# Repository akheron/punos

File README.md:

# Punos

Punos is a suite of home automation devices.

This is a learning project and work in progress.

The goal of the project is learning while building useful devices. Learning
areas include electronics design, KiCad, electronics assembly by hand tools,
what is possible and what is not in electronics, microcontroller capabilities
and firmware develpment.

Design drivers, in no particular order:
- Devices should be useful to me
- Devices are battery powered when it makes sense, with a long battery life
- Wireless communication range should cover ~30-50 m, from building to building
- PCBs are cheap to manufacture
- Components are relatively cheap
- Firmware is written in Rust

See [hardware](hardware/) for currently released boards.

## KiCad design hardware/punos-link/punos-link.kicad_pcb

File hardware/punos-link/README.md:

# punos-link

Punos-link publishes data from punos devices to MQTT over Ethernet.

Features:
- MCU: STM32G071
- Connectivity: TI CC1101 + 868 MHz trace antenna
- Ethernet: WizNet W5500, Hanrun HR911105A
- External flash: 512 KB SPI NOR (for firmware updates over Ethernet)
- Power: 5V / 300 mA

KiCanvas:
- [View schematic](https://kicanvas.org/?repo=https%3A%2F%2Fgithub.com%2Fakheron%2Fpunos%2Fblob%2Fmain%2Fhardware%2Fpunos-link%2Fpunos-link.kicad_sch)
- [View PCB](https://kicanvas.org/?repo=https%3A%2F%2Fgithub.com%2Fakheron%2Fpunos%2Fblob%2Fmain%2Fhardware%2Fpunos-link%2Fpunos-link.kicad_pcb)

License: [CERN-OHL-P](LICENSE.txt), except [CC BY-SA](LICENSE-3RD-PARTY.md) for files in [lib/3dmodels/](lib/3dmodels/).

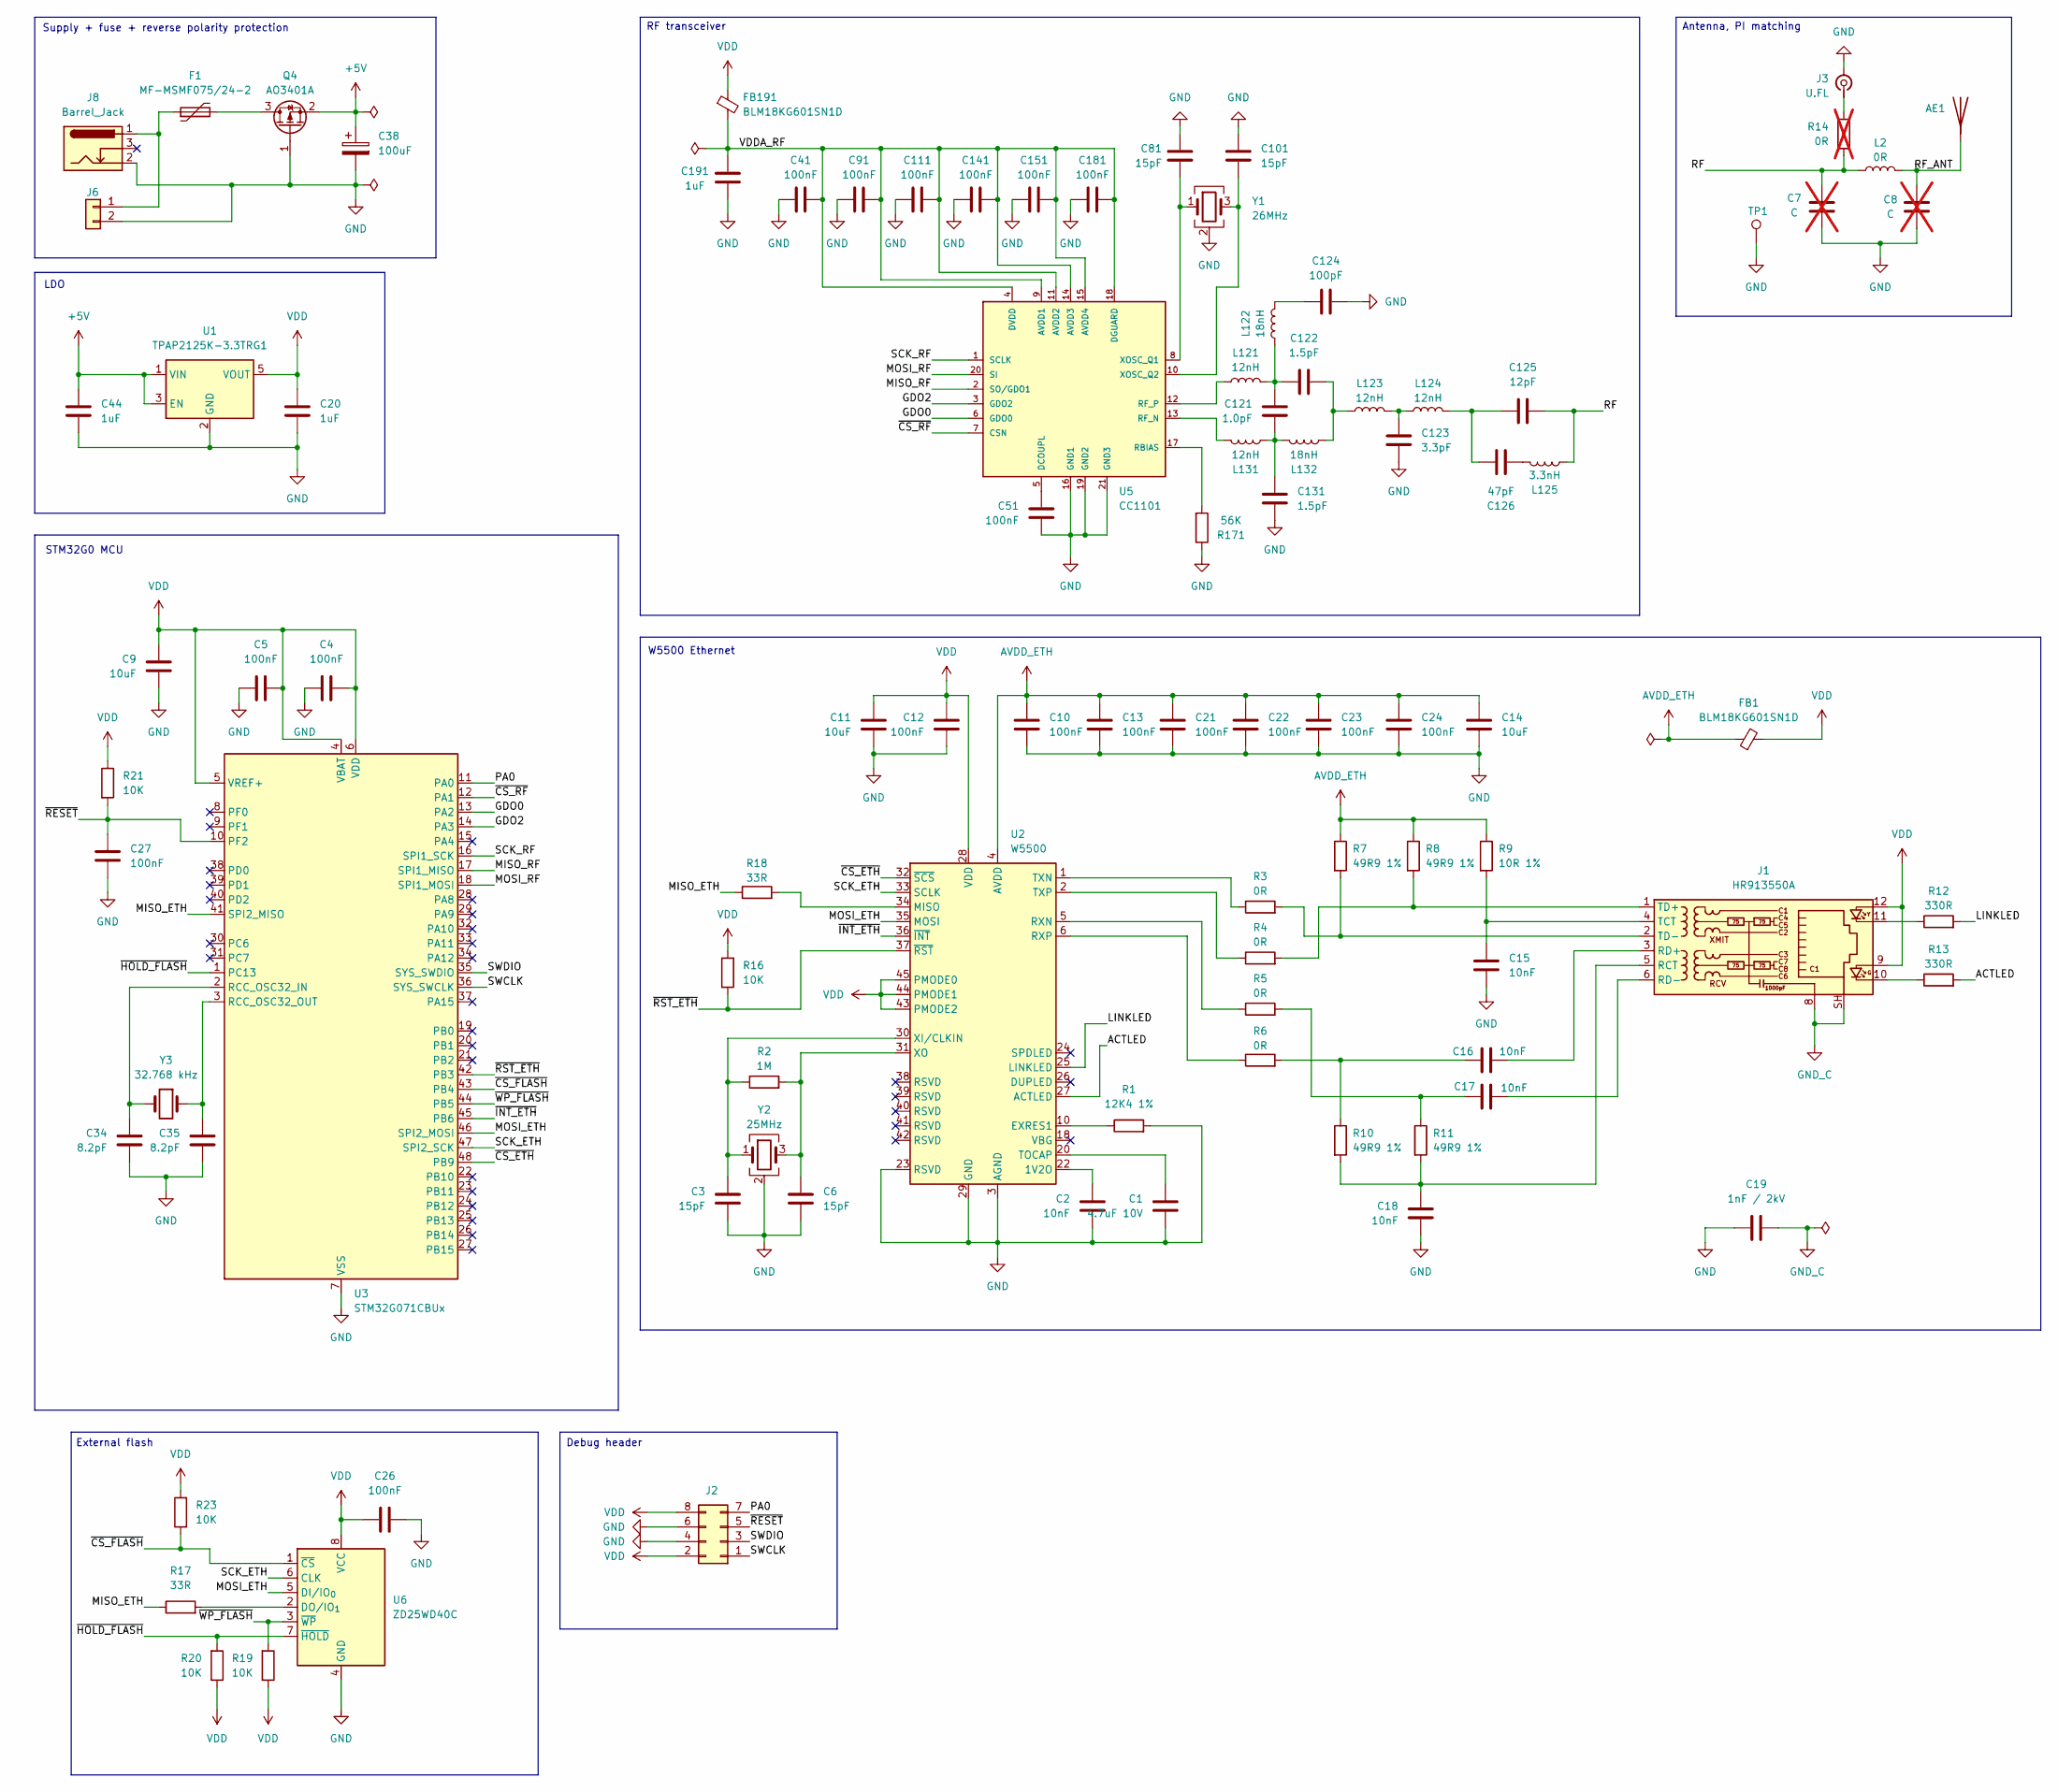
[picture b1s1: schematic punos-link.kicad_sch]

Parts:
AE1: Pin_D0.9mm_L10.0mm_W2.4mm_FlatFork
C1: 4.7uF 10V; C_0603_1608Metric
C2, C15, C16, C17, C18: 10nF; C_0603_1608Metric
C3, C6, C81, C101: 15pF; C_0402_1005Metric; LCSC C76950
C4, C5, C10, C12, C13, C21, C22, C23, C24, C26: 100nF; C_0603_1608Metric
C7, C8: C; C_0402_1005Metric; not fitted
C9, C11, C14: 10uF; C_0603_1608Metric
C19: 1nF / 2kV; C_1808_4520Metric; LCSC C76916
C20, C44, C191: 1uF; C_0603_1608Metric
C27: 100nF; C_0603_1608Metric; LCSC C77055
C34, C35: 8.2pF; C_0402_1005Metric; LCSC C76984
C38: 100uF; CP_Radial_D6.3mm_P2.50mm; LCSC C46471651
C41, C51, C91, C111, C141, C151, C181: 100nF; C_0402_1005Metric; LCSC C77020
C121: 1.0pF; C_0402_1005Metric; LCSC C76953
C122, C131: 1.5pF; C_0402_1005Metric; LCSC C76958
C123: 3.3pF; C_0402_1005Metric; LCSC C76968
C124: 100pF; C_0402_1005Metric; LCSC C77177
C125: 12pF; C_0402_1005Metric; LCSC C76948
C126: 47pF; C_0402_1005Metric; LCSC C76970
F1: MF-MSMF075/24-2; Fuse_1812_4532Metric; LCSC C208467
FB1, FB191: BLM18KG601SN1D; L_0603_1608Metric; LCSC C85833
J1: HR913550A; RJ45_Hanrun_HR911105A_Horizontal; LCSC C163507
J2: Conn_02x04; PinHeader_2x04_P2.54mm_Vertical
J3: U.FL; BAT-WIRELESS-BWU.FL-IPEX1; LCSC C5137195
J6: Conn_01x02; PinHeader_2x01_P2.54mm_Vertical
J8: Barrel_Jack; TLZWLA-DC-005
L2: 0R; L_0402_1005Metric; LCSC C106231
L121, L123, L124, L131: 12nH; L_0402_1005Metric; LCSC C86128
L122, L132: 18nH; L_0402_1005Metric; LCSC C91622
L125: 3.3nH; L_0402_1005Metric; LCSC C3223325
Q4: AO3401A; SOT-23; LCSC C15127
R1: 12K4 1%; R_0603_1608Metric
R2: 1M; R_0603_1608Metric
R3, R4, R5, R6: 0R; R_0603_1608Metric
R7, R8, R10, R11: 49R9 1%; R_0603_1608Metric
R9: 10R 1%; R_0603_1608Metric
R12, R13: 330R; R_0603_1608Metric
R14: 0R; R_0402_1005Metric; not fitted
R16, R19, R20, R21, R23: 10K; R_0603_1608Metric
R17, R18: 33R; R_0603_1608Metric
R171: 56K; R_0603_1608Metric; LCSC C114630
TP1: TestPoint; TestPoint_Pad_D2.5mm
U1: TPAP2125K-3.3TRG1; SOT-23-5; LCSC C49451997
U2: W5500; LQFP-48_7x7mm_P0.5mm; LCSC C32843
U3: STM32G071CBUx; QFN-48-1EP_7x7mm_P0.5mm_EP5.6x5.6mm; LCSC C529343
U5: CC1101; Texas_RGP0020H_VQFN-20-1EP_4x4mm_P0.5mm_EP2.4x2.4mm; LCSC C2654650
U6: ZD25WD40C; SOIC-8_3.9x4.9mm_P1.27mm; LCSC C55863470
Y1: 26MHz; Crystal_SMD_3225-4Pin_3.2x2.5mm; LCSC C5444608
Y2: 25MHz; Crystal_SMD_3225-4Pin_3.2x2.5mm; LCSC C70582
Y3: 32.768 kHz; Crystal_SMD_3215-2Pin_3.2x1.5mm; LCSC C94674

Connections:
+5V: C38.1, C44.1, Q4.2 (S), U1.1 (VIN), U1.3 (EN)
/ACTLED: R13.2, U2.27 (ACTLED)
/GDO0: U3.13 (PA2), U5.6 (GDO0)
/GDO2: U3.14 (PA3), U5.3 (GDO2)
/LINKLED: R12.2, U2.25 (LINKLED)
/MISO_ETH: R17.1, R18.1, U3.41 (SPI2_MISO)
/MISO_RF: U3.17 (SPI1_MISO), U5.2 (SO/GDO1)
/MOSI_ETH: U2.35 (MOSI), U3.46 (SPI2_MOSI), U6.5 (DI/IO_{0})
/MOSI_RF: U3.18 (SPI1_MOSI), U5.20 (SI)
/PA0: J2.7, U3.11 (PA0)
/RF: C7.1, C125.2, L2.2, L125.1, R14.2
/RF_ANT: AE1.1, C8.1, L2.1
/SCK_ETH: U2.33 (SCLK), U3.47 (SPI2_SCK), U6.6 (CLK)
/SCK_RF: U3.16 (SPI1_SCK), U5.1 (SCLK)
/SWCLK: J2.1, U3.36 (SYS_SWCLK)
/SWDIO: J2.3, U3.35 (SYS_SWDIO)
/VDDA_RF: C41.2, C91.2, C111.2, C141.2, C151.2, C181.2, C191.2, FB191.2, U5.4 (DVDD), U5.9 (AVDD1), U5.11 (AVDD2), U5.14 (AVDD3), U5.15 (AVDD4), U5.18 (DGUARD)
/~CS_ETH: U2.32 (~SCS), U3.48 (PB9)
/~CS_FLASH: R23.1, U3.43 (PB4), U6.1 (~CS)
/~CS_RF: U3.12 (PA1), U5.7 (CSN)
/~HOLD_FLASH: R20.2, U3.1 (PC13), U6.7 (~HOLD)
/~INT_ETH: U2.36 (~INT), U3.45 (PB6)
/~RESET: C27.1, J2.5, R21.2, U3.10 (PF2)
/~RST_ETH: R16.2, U2.37 (~RST), U3.42 (PB3)
/~WP_FLASH: R19.2, U3.44 (PB5), U6.3 (~WP)
AVDD_ETH: C10.1, C13.1, C14.1, C21.1, C22.1, C23.1, C24.1, FB1.1, R7.1, R8.1, R9.1, U2.4 (AVDD), U2.8 (AVDD), U2.11 (AVDD), U2.15 (AVDD), U2.17 (AVDD), U2.21 (AVDD)
GND: C1.2, C2.2, C3.2, C4.1, C5.1, C6.2, C7.2, C8.2, C9.1, C10.2, C11.1, C12.2, C13.2, C14.2, C15.2, C18.2, C19.1, C20.2, C21.2, C22.2, C23.2, C24.2, C26.2, C27.2, C34.2, C35.2, C38.2, C41.1, C44.2, C51.2, C81.1, C91.1, C101.1, C111.1, C123.2, C124.1, C131.1, C141.1, C151.1, C181.1, C191.1, J2.4, J2.6, J3.2 (Ext), J6.2, J8.2, Q4.1 (G), R1.2, R171.1, TP1.1 (1_1), U1.2 (GND), U2.3 (AGND), U2.9 (AGND), U2.14 (AGND), U2.16 (AGND), U2.19 (AGND), U2.23 (RSVD), U2.29 (GND), U2.48 (AGND), U3.7 (VSS), U3.49 (VSS), U5.16 (GND1), U5.19 (GND2), U5.21 (GND3), U6.4 (GND), Y1.2 (G), Y1.4 (G), Y2.2 (G), Y2.4 (G)
GND_C: C19.2, J1.8, J1.SH
unnamed: C16.2, R6.2, R10.1
unnamed: C17.2, R5.2, R11.1
unnamed: C121.1, C131.2, L131.2, L132.1
unnamed: C121.2, C122.1, L121.1, L122.1
unnamed: C122.2, L123.2, L132.2
unnamed: C123.1, L123.1, L124.2
unnamed: C124.2, L122.2
unnamed: C125.1, C126.1, L124.1
unnamed: C126.2, L125.2
unnamed: J1.10, R13.1
unnamed: J1.11, R12.1
unnamed: C18.1, J1.5 (RCT), R10.2, R11.2
unnamed: C16.1, J1.3 (RD+)
unnamed: C17.1, J1.6 (RD-)
unnamed: C15.1, J1.4 (TCT), R9.2
unnamed: J1.1 (TD+), R4.2, R8.2
unnamed: J1.2 (TD-), R3.2, R7.2
unnamed: J3.1 (In), R14.1
unnamed: F1.1, J6.1, J8.1
unnamed: F1.2, Q4.3 (D)
unnamed: C2.1, U2.22 (1V2O)
unnamed: R1.1, U2.10 (EXRES1)
unnamed: R18.2, U2.34 (MISO)
unnamed: R5.1, U2.5 (RXN)
unnamed: R6.1, U2.6 (RXP)
unnamed: C1.1, U2.20 (TOCAP)
unnamed: R3.1, U2.1 (TXN)
unnamed: R4.1, U2.2 (TXP)
unnamed: C3.1, R2.1, U2.30 (XI/CLKIN), Y2.1
unnamed: C6.1, R2.2, U2.31 (XO), Y2.3
unnamed: C34.1, U3.2 (RCC_OSC32_IN), Y3.2
unnamed: C35.1, U3.3 (RCC_OSC32_OUT), Y3.1
unnamed: C51.1, U5.5 (DCOUPL)
unnamed: R171.2, U5.17 (RBIAS)
unnamed: L131.1, U5.13 (RF_N)
unnamed: L121.2, U5.12 (RF_P)
unnamed: C81.2, U5.8 (XOSC_Q1), Y1.1
unnamed: C101.2, U5.10 (XOSC_Q2), Y1.3
unnamed: R17.2, U6.2 (DO/IO_{1})
VDD: C4.2, C5.2, C9.2, C11.2, C12.1, C20.1, C26.1, FB1.2, FB191.1, J1.9, J1.12, J2.2, J2.8, R16.1, R19.1, R20.1, R21.1, R23.2, U1.5 (VOUT), U2.28 (VDD), U2.43 (PMODE2), U2.44 (PMODE1), U2.45 (PMODE0), U3.4 (VBAT), U3.5 (VREF+), U3.6 (VDD), U6.8 (VCC)

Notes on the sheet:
LDO
External flash
Supply + fuse + reverse polarity protection
RF transceiver
W5500 Ethernet
STM32G0 MCU
Antenna, PI matching
Debug header

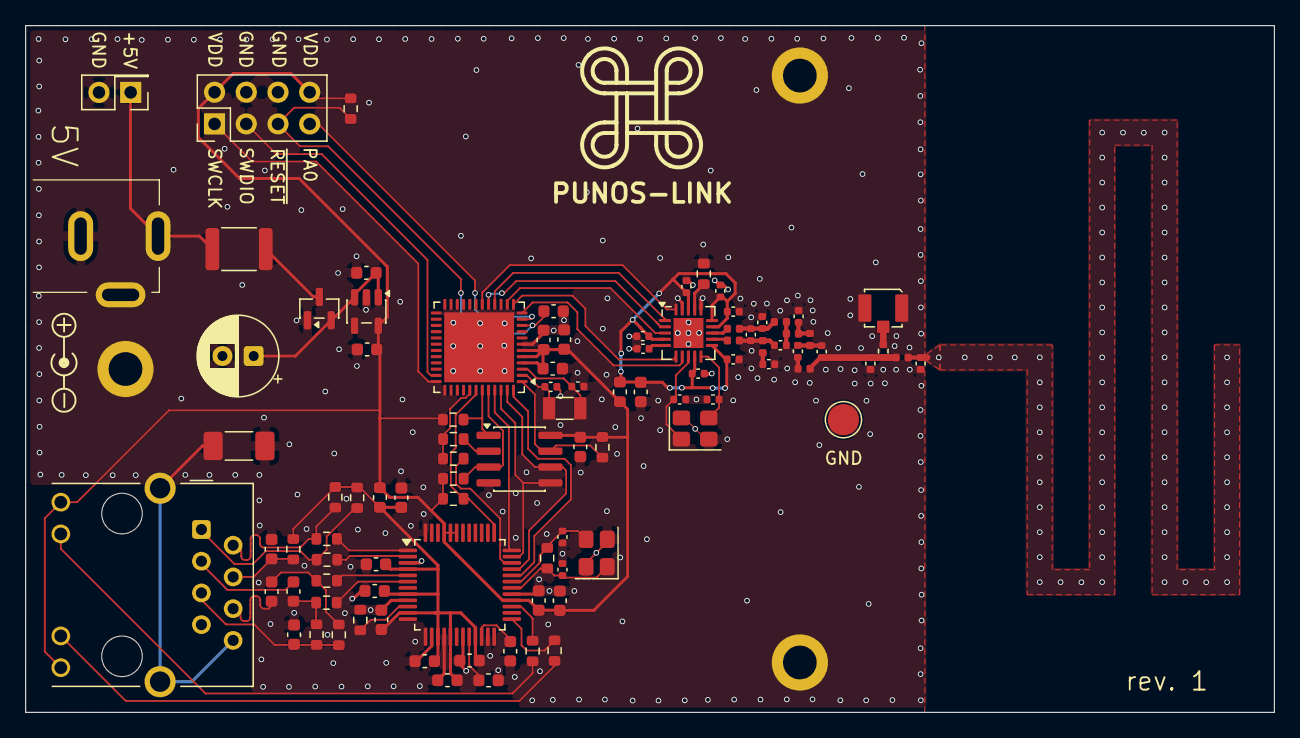
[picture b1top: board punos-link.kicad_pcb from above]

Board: 2 copper layers, 100.0 x 55.0 mm, 95 parts (0 on the bottom side), 68 nets.
